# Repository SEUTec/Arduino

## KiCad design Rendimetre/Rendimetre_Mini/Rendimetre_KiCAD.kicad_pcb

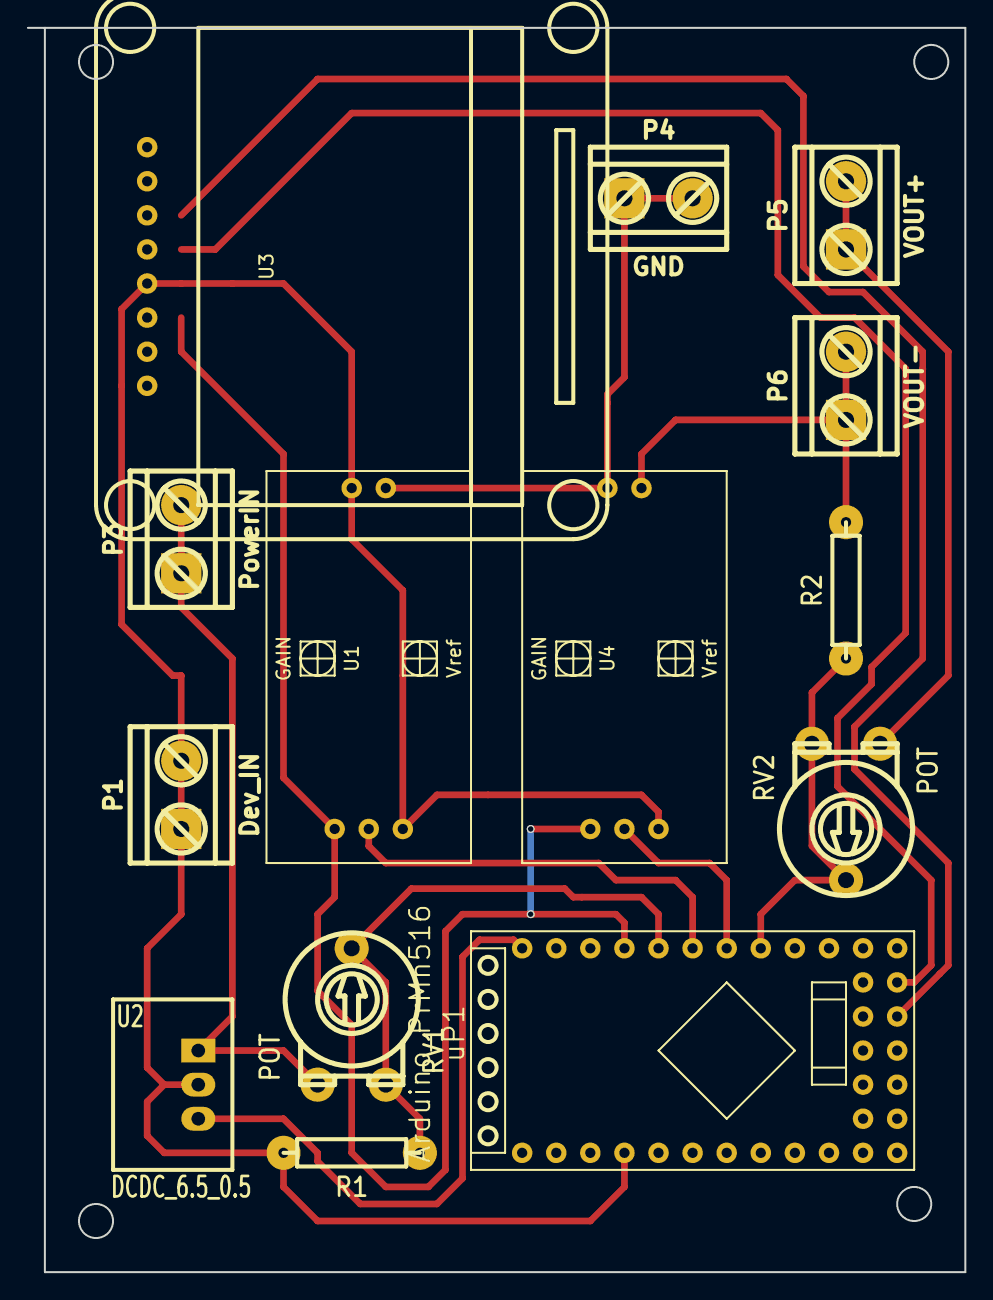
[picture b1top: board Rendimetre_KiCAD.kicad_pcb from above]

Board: 2 copper layers, 69.9 x 92.7 mm, 14 parts (0 on the bottom side), 12 nets.

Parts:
P1: Dev_IN; RGLT2
P3: PowerIN; RGLT2
P4: GND; RGLT2
P5: VOUT+; RGLT2
P6: VOUT-; RGLT2
R1, R2: R; R0.25W
RV1, RV2: POT
U1, U4: ACS712_Low_Current
U2: DCDC_6.5_0.5; DCDC_78xx
U3: OLED_WaveShare; OLED_WaveShare_130
uP1: Arduino_PrMn516; ArduProMini_5V_16MHz

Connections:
/SCL: U3.4, U3.5, U4.4, uP1.21, uP1.22, uP1.28
GND: P1.2, P3.1, R1.2, U1.5, U2.GND, U3.2, U3.6, U4.5, uP1.4
unnamed: P1.1, U1.2
unnamed: P3.2, RV1.1, U1.1, U2.VI
unnamed: P4.1, P4.2
unnamed: P5.1, P5.2, RV2.1
unnamed: P6.1, P6.2, R2.2, U4.1
unnamed: R1.1, RV1.2, RV1.3, uP1.30
unnamed: R2.1, RV2.2, RV2.3, uP1.27
unnamed: U1.4, uP1.29
unnamed: U2.VO, uP1.34
unnamed: U3.1, U4.3

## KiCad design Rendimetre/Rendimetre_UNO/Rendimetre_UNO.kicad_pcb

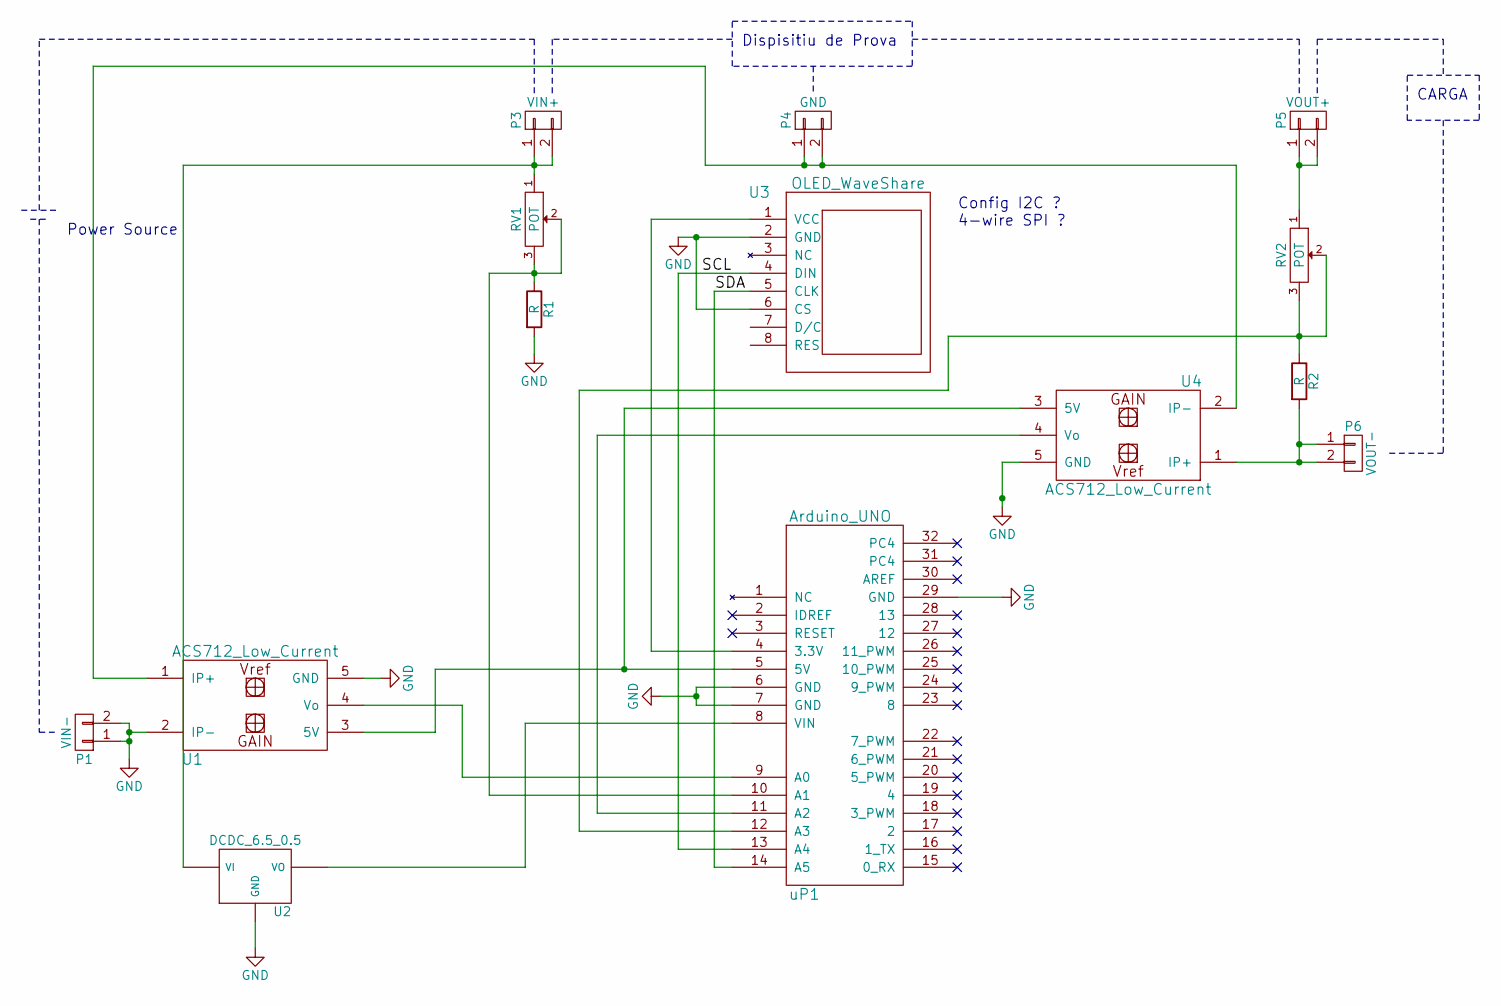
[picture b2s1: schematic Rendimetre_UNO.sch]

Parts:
P1: VIN-; RGLT2
P3: VIN+; RGLT2
P4: GND; RGLT2
P5: VOUT+; RGLT2
P6: VOUT-; RGLT2
R1, R2: R; R0.25W
RV1, RV2: POT
U1, U4: ACS712_Low_Current
U2: DCDC_6.5_0.5; DCDC_78xx
U3: OLED_WaveShare; OLED_WaveShare_130
uP1: Arduino_UNO

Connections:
/SCL: U3.4 (DIN), uP1.13 (A4)
/SDA: U3.5 (CLK), uP1.14 (A5)
GND: P1.1, P1.2, R1.2, U1.2 (IP-), U1.5 (GND), U2.GND, U3.2 (GND), U3.6 (CS), U4.5 (GND), uP1.6 (GND), uP1.7 (GND), uP1.29 (GND)
unnamed: P3.1, P3.2, RV1.1, U2.VI
unnamed: P4.1, P4.2, U1.1 (IP+), U4.2 (IP-)
unnamed: P5.1, P5.2, RV2.1
unnamed: P6.1, P6.2, R2.2, U4.1 (IP+)
unnamed: R1.1, RV1.2, RV1.3, uP1.10 (A1)
unnamed: R2.1, RV2.2, RV2.3, uP1.12 (A3)
unnamed: U1.3 (5V), U4.3 (5V), uP1.5 (5V)
unnamed: U1.4 (Vo), uP1.9 (A0)
unnamed: U2.VO, uP1.8 (VIN)
unnamed: U3.1 (VCC), uP1.4 (3.3V)
unnamed: U4.4 (Vo), uP1.11 (A2)

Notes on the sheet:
Dispisitiu de Prova
CARGA
Power Source
Config I2C ? 4-wire SPI ?

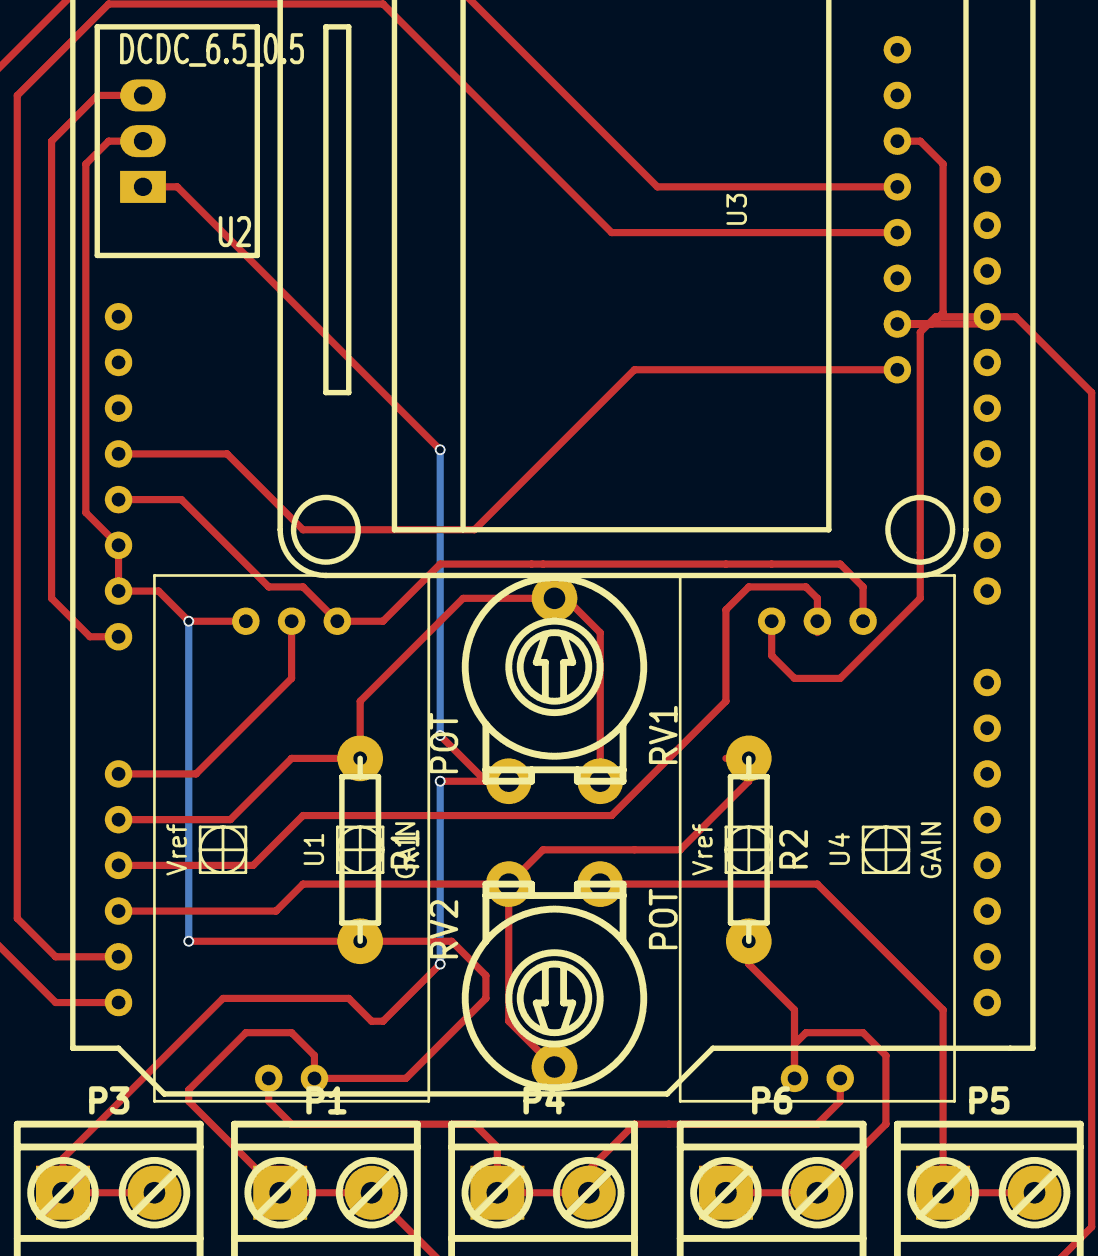
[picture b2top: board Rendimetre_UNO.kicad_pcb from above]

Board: 2 copper layers, 14 parts (0 on the bottom side), 14 nets.
